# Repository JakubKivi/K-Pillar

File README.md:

# K-Pillar

K-Pillar is a fully automated plant watering system controlled by an Arduino Nano with a custom expansion board. It supports up to three independent watering schedules configurable via an LCD and keypad interface, with all settings saved to EEPROM for power-loss resilience. The system also includes a programmable relay for controlling additional devices like grow lights, and is designed with low-power consumption in mind using efficient C++ classes.

More info [here](https://jakubkivi.github.io#portfolio-modal-k-pillar)

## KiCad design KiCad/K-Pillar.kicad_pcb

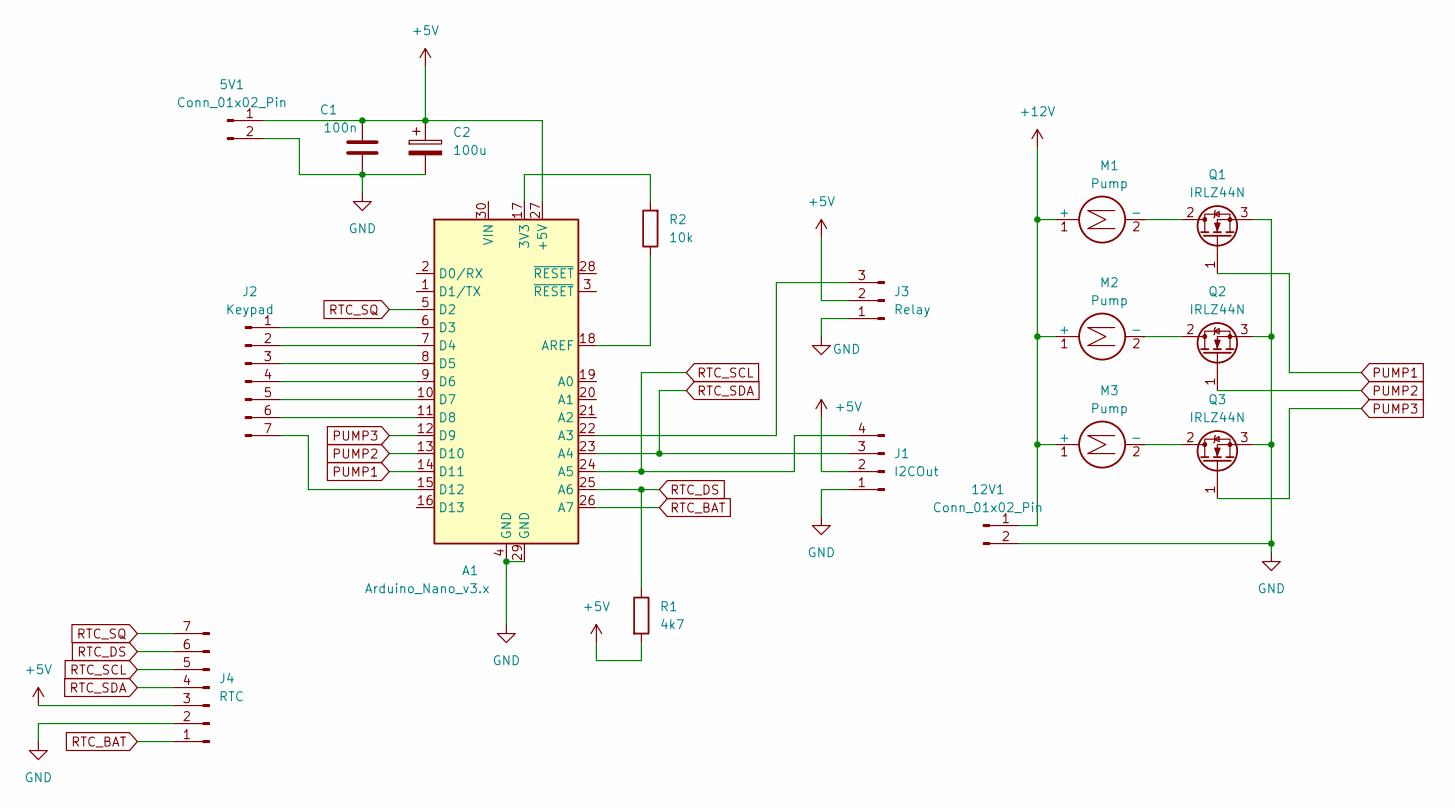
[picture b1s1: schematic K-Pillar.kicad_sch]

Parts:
5V1, 12V1: Conn_01x02_Pin; PinHeader_1x02_P2.54mm_Vertical
A1: Arduino_Nano_v3.x; Arduino_Nano
C1: 100n; C_0805_2012Metric_Pad1.18x1.45mm_HandSolder
C2: 100u; CP_Radial_D5.0mm_P2.50mm
J1: I2COut; PinHeader_1x04_P2.54mm_Vertical
J2: Keypad; PinHeader_1x07_P2.54mm_Vertical
J3: Relay; PinHeader_1x03_P2.54mm_Vertical
J4: RTC; PinHeader_1x07_P2.54mm_Vertical
M1, M2, M3: Pump; TerminalBlock_4Ucon_1x02_P3.50mm_Horizontal
Q1, Q2, Q3: IRLZ44N; TO-220-3_Vertical
R1: 4k7; R_0805_2012Metric_Pad1.20x1.40mm_HandSolder
R2: 10k; R_0805_2012Metric_Pad1.20x1.40mm_HandSolder

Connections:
+5V: 5V1.1, A1.27 (+5V), C1.2, C2.1, J1.2, J3.2, J4.3, R1.2
+12V: 12V1.1, M1.1 (+), M2.1 (+), M3.1 (+)
GND: 5V1.2, 12V1.2, A1.4 (GND), A1.29 (GND), C1.1, C2.2, J1.1, J3.1, J4.2, Q1.3 (S), Q2.3 (S), Q3.3 (S)
unnamed: A1.17 (3V3), R2.2
unnamed: A1.22 (A3), J3.3
unnamed: A1.18 (AREF), R2.1
unnamed: A1.6 (D3), J2.1
unnamed: A1.7 (D4), J2.2
unnamed: A1.8 (D5), J2.3
unnamed: A1.9 (D6), J2.4
unnamed: A1.10 (D7), J2.5
unnamed: A1.11 (D8), J2.6
unnamed: A1.15 (D12), J2.7
unnamed: M1.2 (-), Q1.2 (D)
unnamed: M2.2 (-), Q2.2 (D)
unnamed: M3.2 (-), Q3.2 (D)
PUMP1: A1.14 (D11), Q1.1 (G)
PUMP2: A1.13 (D10), Q2.1 (G)
PUMP3: A1.12 (D9), Q3.1 (G)
RTC_BAT: A1.26 (A7), J4.1
RTC_DS: A1.25 (A6), J4.6, R1.1
RTC_SCL: A1.24 (A5), J1.4, J4.5
RTC_SDA: A1.23 (A4), J1.3, J4.4
RTC_SQ: A1.5 (D2), J4.7

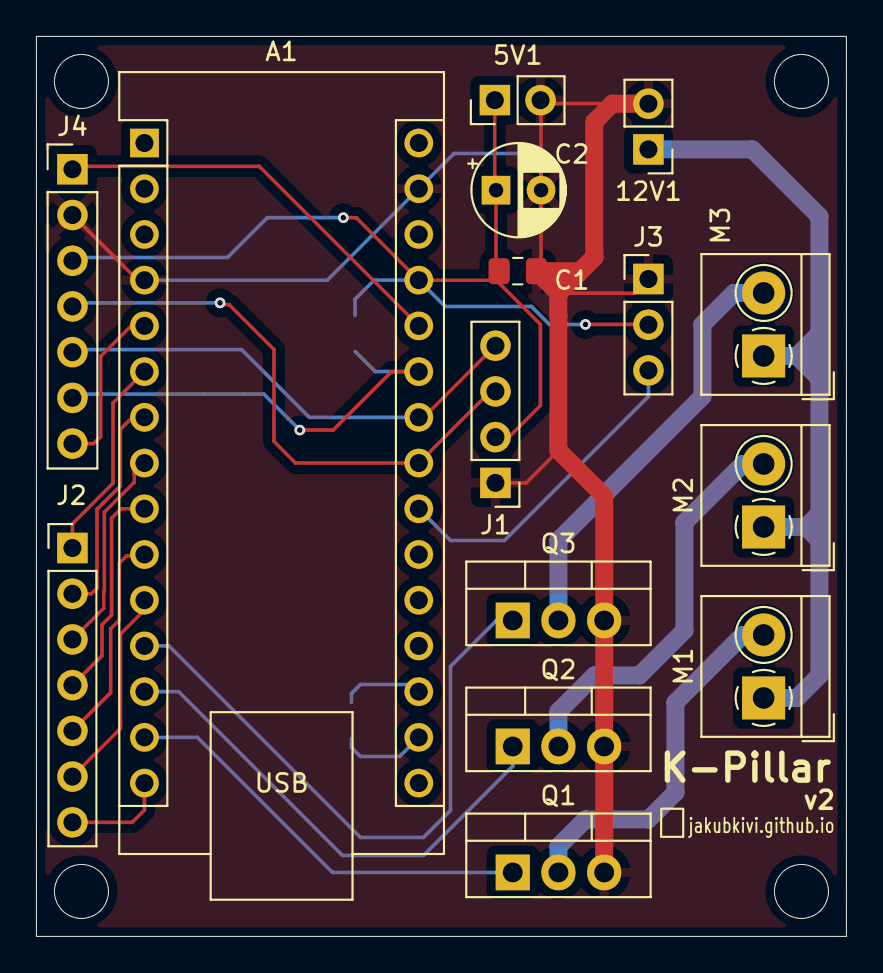
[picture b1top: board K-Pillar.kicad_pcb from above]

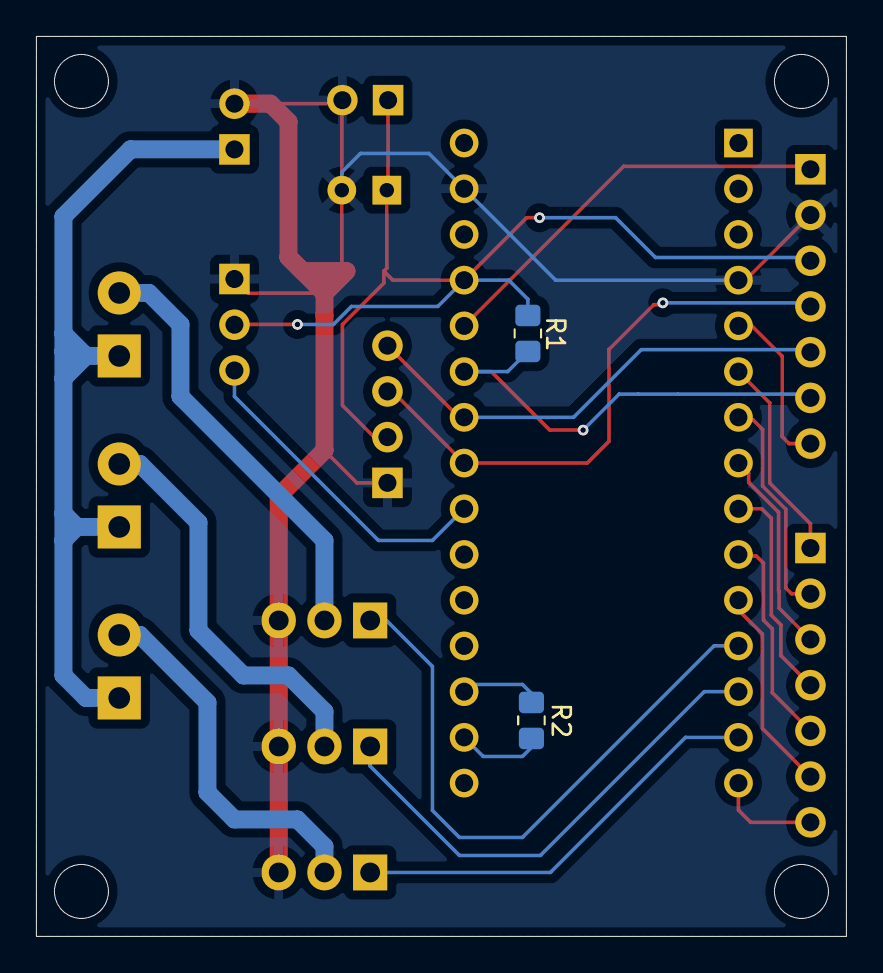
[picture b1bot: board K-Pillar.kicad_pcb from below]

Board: 2 copper layers, 45.0 x 50.0 mm, 17 parts (2 on the bottom side), 24 nets.

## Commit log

2025-02-25 started kicad project
2025-02-28 płytka zrobiona można na narty
2025-03-19 szkic i coś co działa
2025-03-23 working on lcd refresh pointerepere papardele
2025-03-28 improvements
2025-04-06 added submenu
2025-04-14 cleaned and added input
2025-04-14 working on sleeping
2025-04-15 started working on v2 board
2025-04-21 board v2
2025-05-06 new board working
2025-05-07 przywrócenie kicada bo idk co sie stalo ale nic nie bylo + RTC działa w głównym kodzie
2025-05-07 working on ints (xd)
2025-05-09 przerwania działają, schedule i time inprogress
2025-05-09 ifdef time co za bomba
2025-05-10 edycja i zmiana godziny
2025-05-13 Zapisywanie godziny działa, zapisywanie do pamięci działa
2025-05-15 zapisują się schedule do eepromu ale zegar nie chodzi... no ja nie wiem kto, ktoś podpalił. A i jeszcze znowu sie kikad zepsuł o.O sus
2025-05-16 poprawione piny, zegar chodzi, wszystko się zapisuje, bajabongo
2025-05-20 improvments and tests
2025-05-21 datestruct w trakcie
2025-05-24 daty i inne zapisy in progress
2025-05-24 dodane zapisywanie dat, adminflaga, i next watering ale z nim coś nie klika
2025-05-26 chyba wszystko dziala jeszcze tylko potestować i dopracować
2025-05-27 potestowane i pozmieniane, po wstępnych pomyślnych testach
2025-06-02 relayschedule i 3 pompki
2025-06-03 socket logic almost done
2025-06-06 soft v1.0 wszystko wydaje sie działać, sprzątable
2025-06-16 usypianie poprawione ale czasem sie budzi
2025-06-17 finished with new keypad, debugged, closing frame
2025-06-22 updating readme on github
2026-02-03 pipe holder added
2026-02-03 pipe holder v1
2026-02-03 improvements in pipeholder
2026-02-05 updated pipeholder
